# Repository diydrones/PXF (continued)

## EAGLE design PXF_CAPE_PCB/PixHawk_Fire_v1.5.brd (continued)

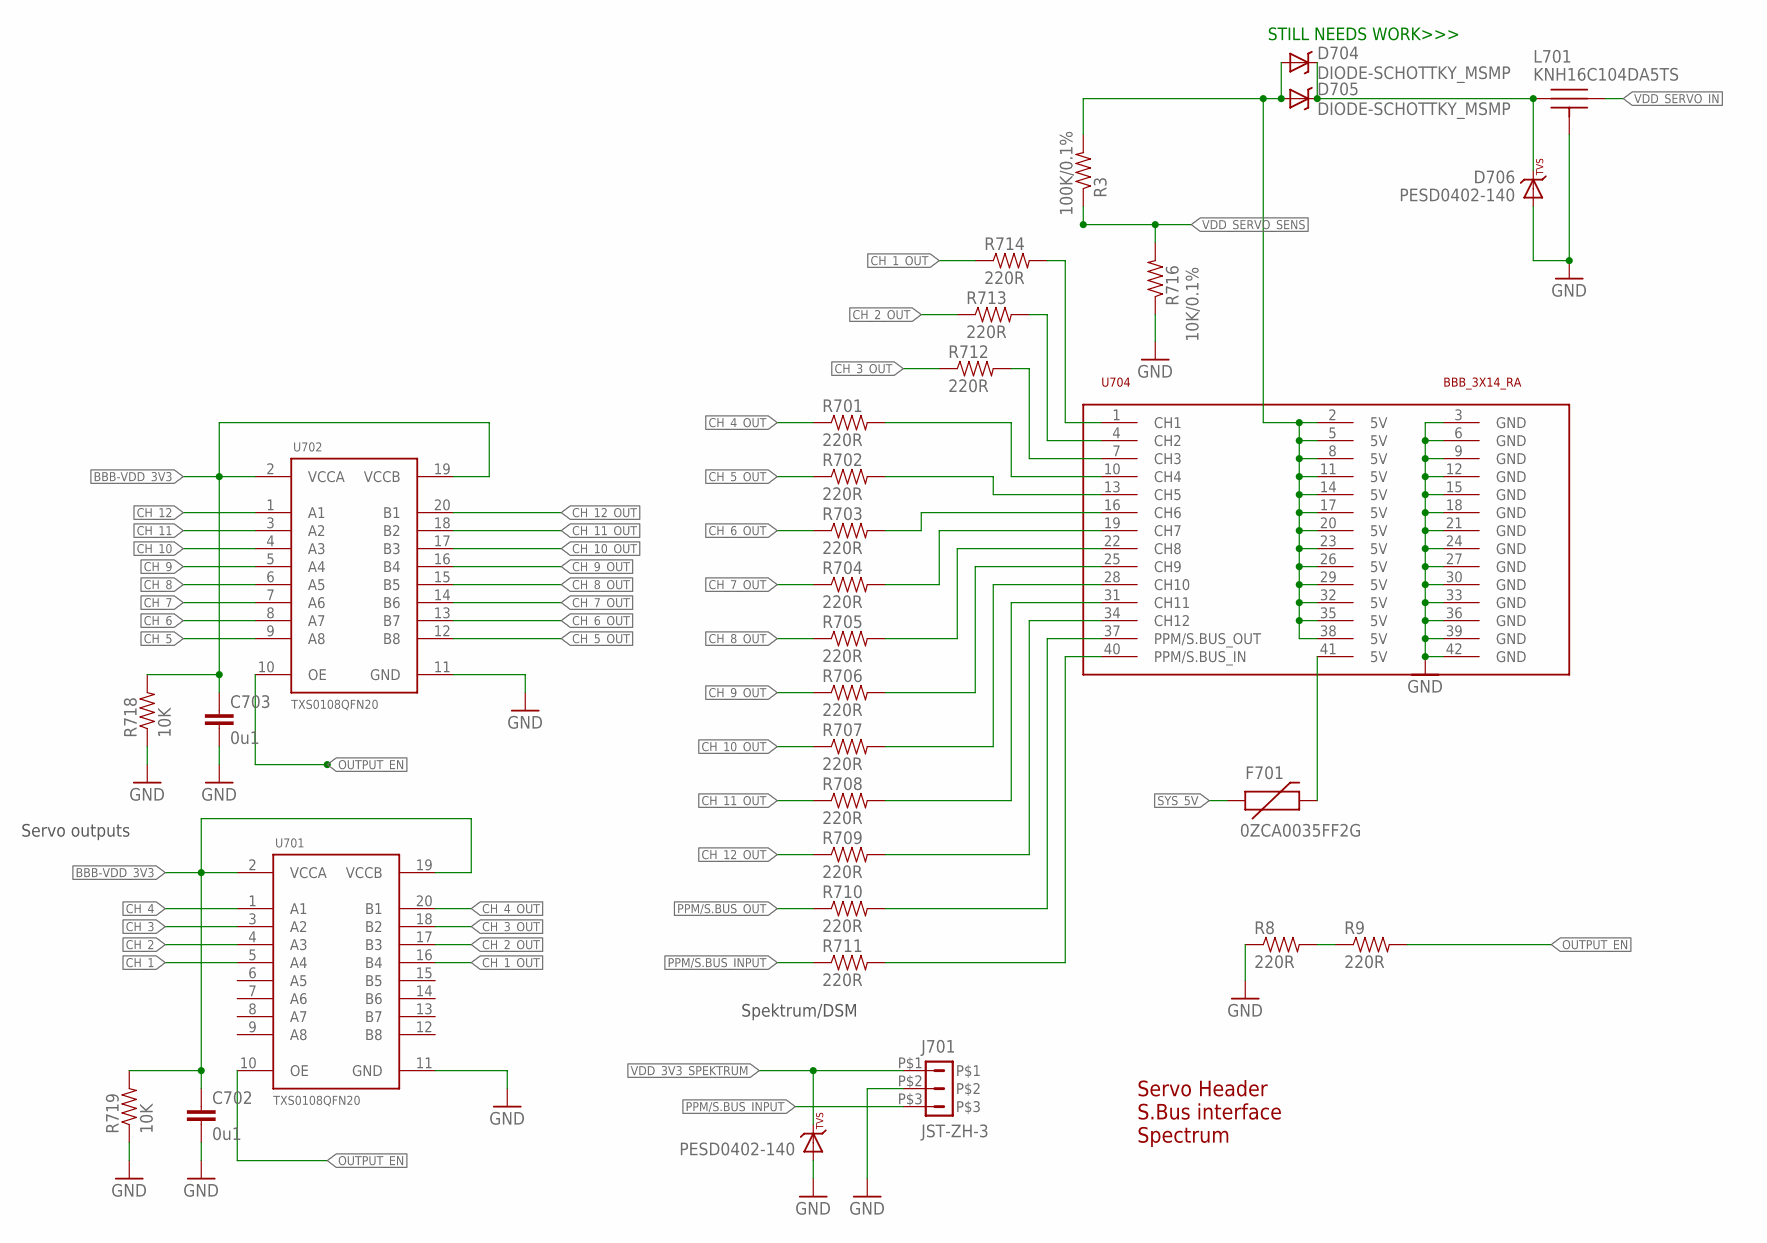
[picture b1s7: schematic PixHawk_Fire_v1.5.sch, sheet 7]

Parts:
C702, C703: 0u1; 0402-CAP; PARTNO CC0402ZRY5V7BB104
D703, D706: PESD0402-140; 0402-TVS; PARTNO PESD0402-140
D704, D705: DIODE-SCHOTTKY_MSMP; MICROSMP; PARTNO SS14
F701: 0ZCA0035FF2G; PTC-1206; PARTNO 0ZCA0035FF2G
J701: JST-ZH-3; JST-ZH-SMT-VERTICAL; PARTNO B3B-ZR-SM4-TF (LF)(SN)(P)
L701: KNH16C104DA5TS; KYOCERA-KNH16-DA; PARTNO KNH16C104DA5TS
R3: 100K/0.1%; 0402-RES; PARTNO ERA-2AEB104X
R8, R9: 220R; 0402-RES; PARTNO RC0402FR-07220RL
R701, R702, R703, R704, R705, R706, R707, R708, R709, R710, R711, R712, R713, R714: 220R; 0402-RES; PARTNO RC0402FR-07120RL
R716: 10K/0.1%; 0402-RES; PARTNO ERA-2AEB103X
R718, R719: 10K; 0402-RES; PARTNO ERA-2AEB103X
U701, U702: TXS0108QFN20; QFN20-RGY; PARTNO TXS0108ERGYR
U704: BBB_3X14_RA; 3X14RA; PARTNO 07579

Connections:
BBB-VDD_3V3: C702.P$1 (1), C703.P$1 (1), R718.P$2 (2), R719.P$2 (2), U701.2 (VCCA), U701.19 (VCCB), U702.2 (VCCA), U702.19 (VCCB); also elsewhere on the board
CH_1: U701.5 (A4); also elsewhere on the board
CH_1_OUT: R714.P$1 (1), U701.16 (B4)
CH_2: U701.4 (A3); also elsewhere on the board
CH_2_OUT: R713.P$1 (1), U701.17 (B3)
CH_3: U701.3 (A2); also elsewhere on the board
CH_3_OUT: R712.P$1 (1), U701.18 (B2)
CH_4: U701.1 (A1); also elsewhere on the board
CH_4_OUT: R701.P$1 (1), U701.20 (B1)
CH_5: U702.9 (A8); also elsewhere on the board
CH_5_OUT: R702.P$1 (1), U702.12 (B8)
CH_6: U702.8 (A7); also elsewhere on the board
CH_6_OUT: R703.P$1 (1), U702.13 (B7)
CH_7: U702.7 (A6); also elsewhere on the board
CH_7_OUT: R704.P$1 (1), U702.14 (B6)
CH_8: U702.6 (A5); also elsewhere on the board
CH_8_OUT: R705.P$1 (1), U702.15 (B5)
CH_9: U702.5 (A4); also elsewhere on the board
CH_9_OUT: R706.P$1 (1), U702.16 (B4)
CH_10: U702.4 (A3); also elsewhere on the board
CH_10_OUT: R707.P$1 (1), U702.17 (B3)
CH_11: U702.3 (A2); also elsewhere on the board
CH_11_OUT: R708.P$1 (1), U702.18 (B2)
CH_12: U702.1 (A1); also elsewhere on the board
CH_12_OUT: R709.P$1 (1), U702.20 (B1)
FMU-CH6-PROT: R708.P$2 (2), U704.31 (CH11)
GND: C702.P$2 (2), C703.P$2 (2), D703.A, D706.A, J701.P$2, L701.P$3, L701.P$4, L701.P$5, R8.P$1 (1), R716.P$1 (1), R718.P$1 (1), R719.P$1 (1), U701.11 (GND), U702.11 (GND), U704.3 (GND), U704.6 (GND), U704.9 (GND), U704.12 (GND), U704.15 (GND), U704.18 (GND), U704.21 (GND), U704.24 (GND), U704.27 (GND), U704.30 (GND), U704.33 (GND), U704.36 (GND), U704.39 (GND), U704.42 (GND); also elsewhere on the board
IO-CH1-PROT: R707.P$2 (2), U704.28 (CH10)
IO-CH8-PROT: R712.P$2 (2), U704.7 (CH3)
unnamed: R8.P$2 (2), R9.P$1 (1)
unnamed: D704.CATHODE (C), D705.CATHODE (C), D706.C, L701.P$1
unnamed: D704.ANODE (A), D705.ANODE (A), R3.P$2 (2), U704.2 (5V), U704.5 (5V), U704.8 (5V), U704.11 (5V), U704.14 (5V), U704.17 (5V), U704.20 (5V), U704.23 (5V), U704.26 (5V), U704.29 (5V), U704.32 (5V), U704.35 (5V), U704.38 (5V)
unnamed: F701.2, U704.41 (5V)
unnamed: R701.P$2 (2), U704.10 (CH4)
unnamed: R709.P$2 (2), U704.34 (CH12)
unnamed: R702.P$2 (2), U704.13 (CH5)
unnamed: R703.P$2 (2), U704.16 (CH6)
unnamed: R704.P$2 (2), U704.19 (CH7)
unnamed: R705.P$2 (2), U704.22 (CH8)
unnamed: R706.P$2 (2), U704.25 (CH9)
unnamed: R710.P$2 (2), U704.37 (PPM/S.BUS_OUT)
unnamed: R711.P$2 (2), U704.40 (PPM/S.BUS_IN)
unnamed: R713.P$2 (2), U704.4 (CH2)
OUTPUT_EN: R9.P$2 (2), U701.10 (OE), U702.10 (OE); also elsewhere on the board
PPM-SBUS-PROT: R714.P$2 (2), U704.1 (CH1)
PPM/S.BUS_INPUT: J701.P$3, R711.P$1 (1); also elsewhere on the board
PPM/S.BUS_OUT: R710.P$1 (1); also elsewhere on the board
SYS_5V: F701.1; also elsewhere on the board
VDD_3V3_SPEKTRUM: D703.C, J701.P$1; also elsewhere on the board
VDD_SERVO_IN: L701.P$2
VDD_SERVO_SENS: R3.P$1 (1), R716.P$2 (2); also elsewhere on the board

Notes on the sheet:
Servo Header S.Bus interface Spectrum
Servo outputs
Spektrum/DSM
STILL NEEDS WORK>>>

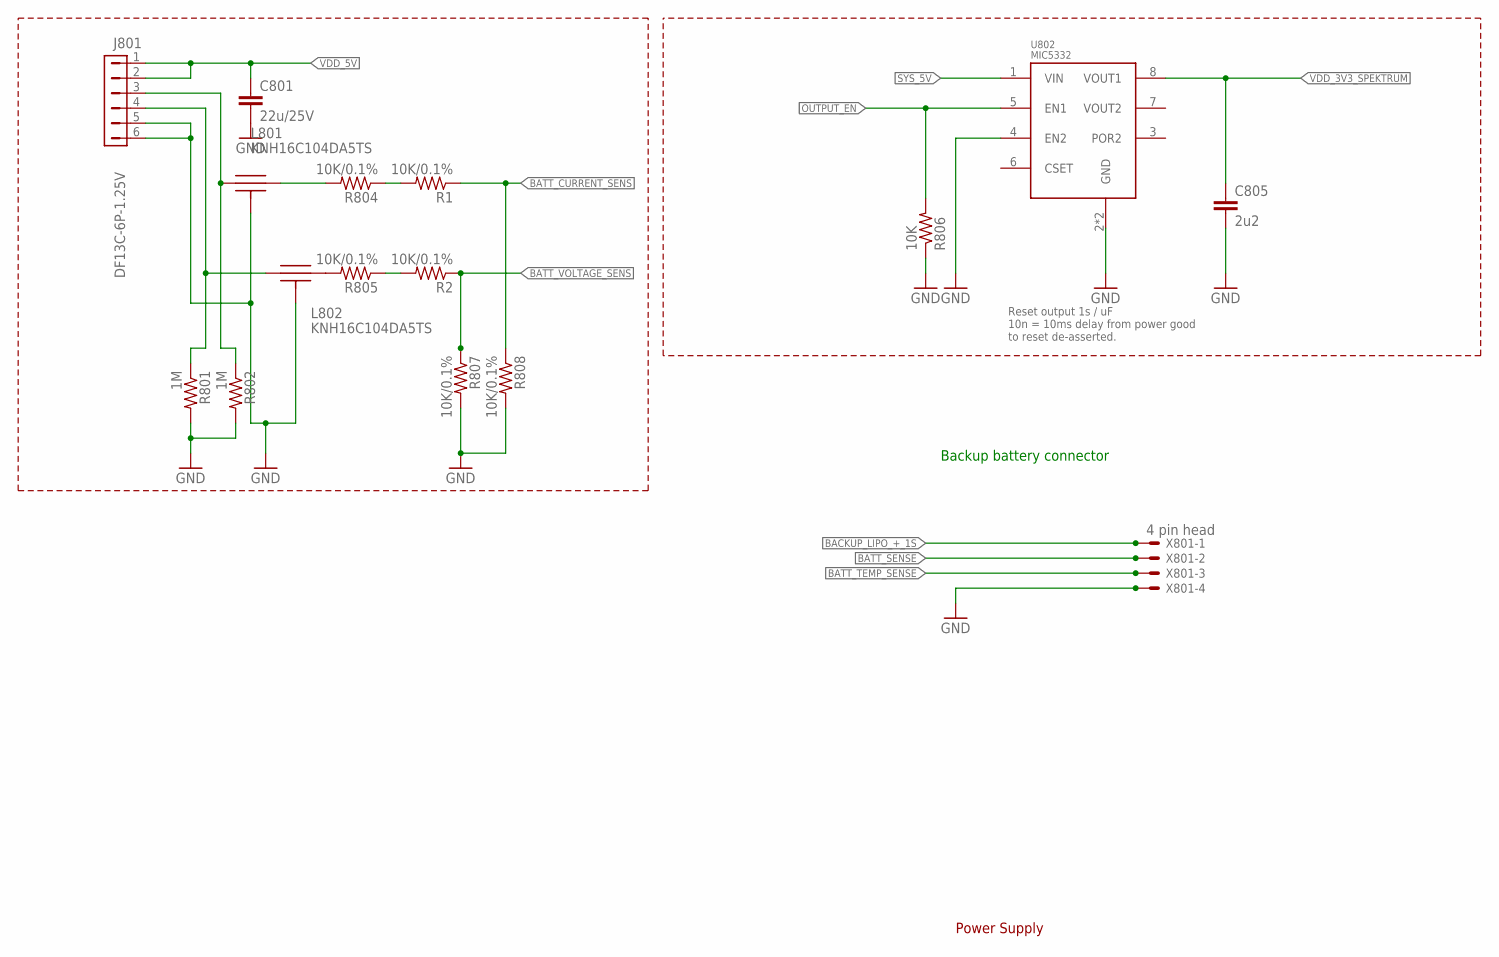
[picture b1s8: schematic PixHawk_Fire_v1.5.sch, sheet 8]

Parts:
C801: 22u/25V; 0805-CAP; PARTNO CL21A226MAQNNNE
C805: 2u2; 0402-CAP; PARTNO CC0603ZRY5V6BB225
J801: DF13C-6P-1.25V; PARTNO DF13C-6P-1.25V(20)
L801, L802: KNH16C104DA5TS; KYOCERA-KNH16-DA; PARTNO KNH16C104DA5TS
R1, R2, R804, R805, R807, R808: 10K/0.1%; 0402-RES; PARTNO ERA-2AEB103X
R801, R802: 1M; 0402-RES; PARTNO RC0402FR-071ML
R806: 10K; 0402-RES; PARTNO ERA-2AEB103X
U802: MIC5332; MLF-8-EPAD; PARTNO MIC5332-SSYMT
X801: 4 pin head; 53047-04; PARTNO 53047-04

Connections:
BACKUP_LIPO_+_1S: X801.1; also elsewhere on the board
BATT_CURRENT_SENS: R1.P$1 (1), R808.P$1 (1); also elsewhere on the board
BATT_CURRENT_SENS_PROT: J801.3, L801.P$1, R802.P$1 (1)
BATT_SENSE: X801.2; also elsewhere on the board
BATT_TEMP_SENSE: X801.3; also elsewhere on the board
BATT_VOLTAGE_SENS: R2.P$1 (1), R807.P$1 (1); also elsewhere on the board
BATT_VOLTAGE_SENS_PROT: J801.4, L802.P$1, R801.P$1 (1)
GND: C801.P$2 (2), C805.P$2 (2), J801.5, J801.6, L801.P$3, L801.P$4, L801.P$5, L802.P$3, L802.P$4, L802.P$5, R801.P$2 (2), R802.P$2 (2), R806.P$1 (1), R807.P$2 (2), R808.P$2 (2), U802.2 (GND), U802.4 (EN2), U802.GND, X801.4; also elsewhere on the board
unnamed: R1.P$2 (2), R804.P$1 (1)
unnamed: R2.P$2 (2), R805.P$1 (1)
unnamed: L802.P$2, R805.P$2 (2)
unnamed: L801.P$2, R804.P$2 (2)
OUTPUT_EN: R806.P$2 (2), U802.5 (EN1); also elsewhere on the board
SYS_5V: U802.1 (VIN); also elsewhere on the board
VDD_3V3_SPEKTRUM: C805.P$1 (1), U802.8 (VOUT1); also elsewhere on the board
VDD_5V: C801.P$1 (1), J801.1, J801.2; also elsewhere on the board

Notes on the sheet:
Power Supply
Reset output 1s / uF 10n = 10ms delay from power good to reset de-asserted.
Backup battery connector

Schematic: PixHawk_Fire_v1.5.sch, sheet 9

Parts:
ADC_PR: PAD.04; PAD.04X.04; PARTNO *
CAN_H: PAD.04; PAD.04X.04; PARTNO *
CAN_L: PAD.04; PAD.04X.04; PARTNO *
GND, GND.: PAD.04; PAD.04X.04; PARTNO *
JP901, JP902: FIDUCIAL1.5X3; FIDUCIAL-1.5X3; PARTNO *
M3_MOUNT901, M3_MOUNT902, M3_MOUNT903, M3_MOUNT904: MOUNT-HOLE3.1MM; MOUNT-HOLE3.1; PARTNO *
OSHW_LOGO: OSHW-LOGOS; OSHW-LOGO-S; PARTNO *
S1RX, S1TX, S2RX, S2TX: PAD.04; PAD.04X.04; PARTNO *
VDDA_3V901: PAD.04; PAD.04X.04; PARTNO *
VDD_3V901, VDD_5V_BRICK, VDD_5V_IN: PAD.04; PAD.04X.04; PARTNO *

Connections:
BBB-VDD_3V3: VDD_3V901.P$1; also elsewhere on the board
CAN_H: CAN_H.P$1; also elsewhere on the board
CAN_L: CAN_L.P$1; also elsewhere on the board
GND: GND.P$1, GND..P$1; also elsewhere on the board
PRESSURE_SENS_IN: ADC_PR.P$1; also elsewhere on the board
SYS_5V: VDD_5V_IN.P$1; also elsewhere on the board
TTYO4_RX: S1RX.P$1; also elsewhere on the board
TTYO4_TX: S1TX.P$1; also elsewhere on the board
TTYO5_RX: S2RX.P$1; also elsewhere on the board
TTYO5_TX: S2TX.P$1; also elsewhere on the board
VDD_3V3_SENSORS: VDDA_3V901.P$1; also elsewhere on the board
VDD_5V: VDD_5V_BRICK.P$1; also elsewhere on the board

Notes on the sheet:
Mounting holes to suit M3 fastener
and Richco R908 series spacer.
Use R908-5 spacers to stack with
other PX4 series boards (7.95 mm).
Production Testing Pads
Test and Fiducials
Minimum drill: 0.3 mm
Minimum trace width (use mm for traces): 0.15 mm
Minimum copper distance (all signals): 0.15 mm
Dimension / hole minimum distance: 0.2 mm
Layout grid: 4 mil, part grid: 4 mil. Dimensions / hole positions: 0.5 mm
Board: FR4 black, 1.0 mm. Solder stop on vias < 0.6 mm.
Signoff rules: Footprint checked, pinmap checked, schematic checked, cross-references to other pages checked.
Routing: 1: general/escape 2: ground 3: horizontal 4: vertical 5: power 6: general/escape
Fiducials for machine vision alignment.
Parts: Resistors: 0402 / 1% unless specified otherwise Capacitors: 0402 to 1206, ceramic, voltage rating: 10V unless specified

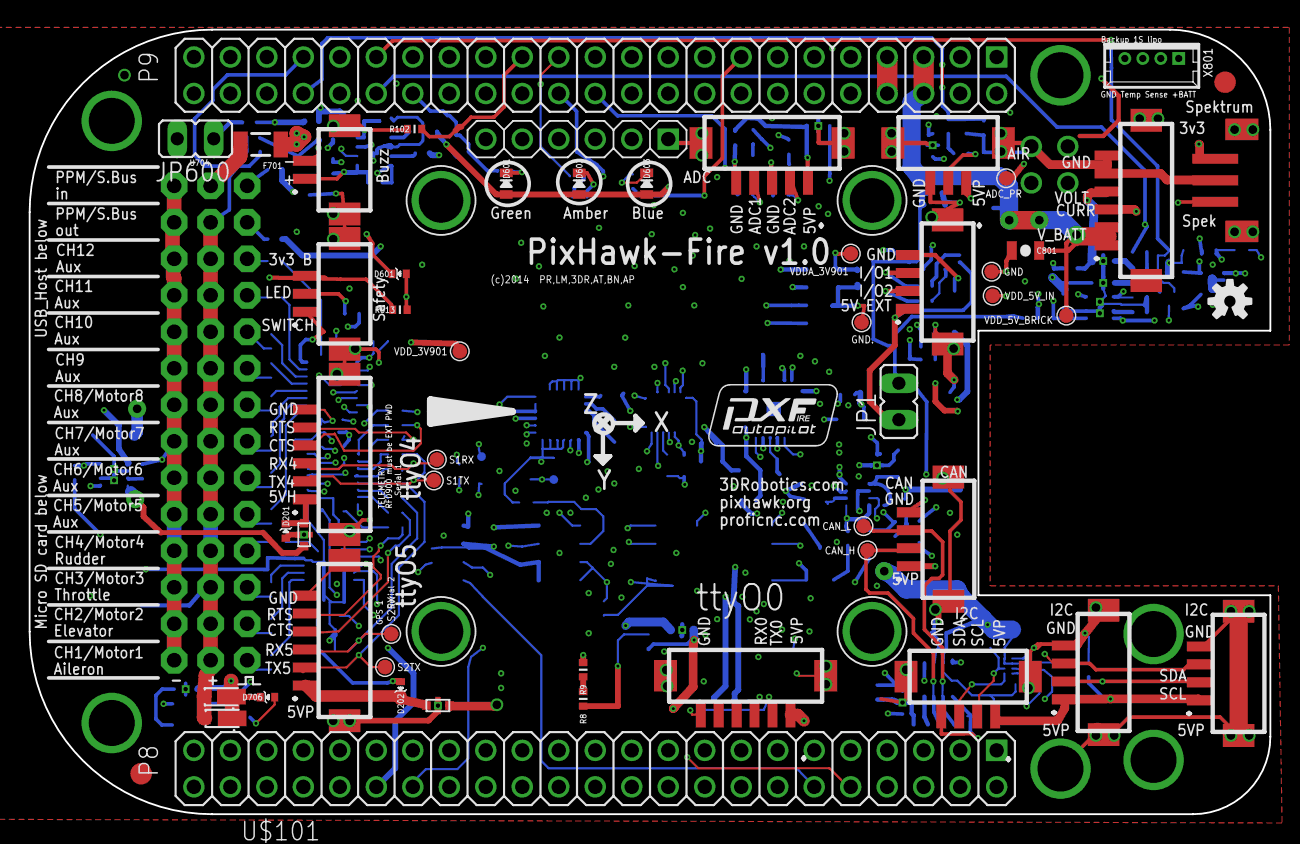
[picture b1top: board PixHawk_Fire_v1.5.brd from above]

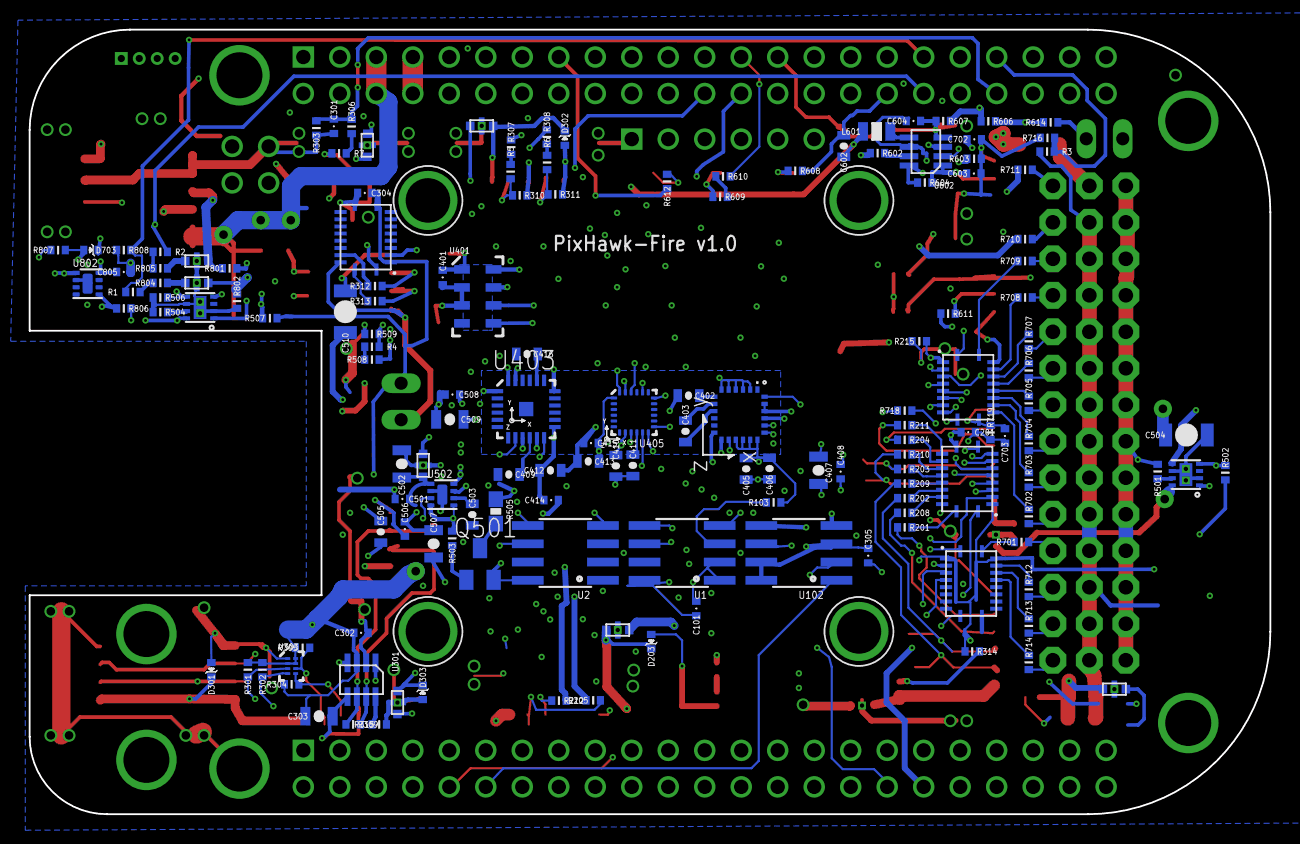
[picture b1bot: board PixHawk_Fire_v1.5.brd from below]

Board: 6 copper layers, 86.4 x 54.6 mm, 206 parts (149 on the bottom side), 177 nets.

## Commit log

2014-02-17 Update README.md
    Added some information.
2014-04-27 Added planning doccuments, Schematic, and PCB files
2014-04-28 added Device Tree
2014-05-07 added licence information
2014-05-15 maked good sensors with green
2014-05-15 Added PDF for reference
2014-05-30 Started v1.1
2014-07-03 added 3dr template
2014-10-08 Version 1.4, up to date, all fixes merged.
2014-10-08 Update README.md
    fixed a typo
2014-10-09 fixed issue with capacitor on the MPU9250 value was incorrect
2014-10-29 fixed missing ground on Serial 3 plug
2014-11-27 moved to version 1.5 fixed UART BUG
2014-11-27 added a change record
2014-12-24 Added Gitter badge
2015-01-15 Update LICENSE
2018-10-16 Noticed a minor spelling mistake
